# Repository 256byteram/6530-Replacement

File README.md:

# 6530 Replacement

Replaces the 6530 ICs found on early revision Allied Leisure pinball machines.

## Components

Please note these designs and instructions come with absolutely no warranty, implied or otherwise. I write these instructions assuming the builder has experience in assembling electronics.

You will need:

- x1 27C64 EPROM (or equivalent)

- x1 28 pin DIP IC socket

- x2 6532 IC's

- x5 40 pin IC socket - Dual wipe, **not machined**

- x1 74LS42 DIP IC

- x1 16 pin DIP IC socket

- x1 74LS11 DIP IC

- x2 74LS00 DIP IC

- x3 14 pin DIP IC socket

- x6 1N4148 silicon diodes

- x1 2N7000 transistor

- x3 1k ohm 1/4W resistors

- x1 1k x6 resistor network (or alternatively an additional 6 1k ohm 1/4W resistors)

- x6 100nF 50V monolithic capacitors

- x100 pin headers to fit the original sockets on the CPU board (5 rows of 20 pins)

- Alternatively: x5 stackable headers for the ESP32 [Sparkfun part number PRT-14311](https://www.sparkfun.com/esp32-thing-stackable-header-set.html). These won't damage IC sockets. See *Construction Notes* below.

To have these boards manufactured, it should be as simple as zipping the 6530-Replacement-Gerber folder and submitting them to a PCB manufacturer. The board dimensions are 100.3 x 100.3mm

## ROMs

I can not host the ROM image here as they are copyrighted. I have supplied a 1k blank image to assist with generating the required ROM image.

There are three ROM binaries I was supplied with, one each from the three original 6530's:

- EE1712_82219_DG_MOS6530_009.bin

- EE1712_82219_DG_MOS6530_010.bin

- EE1712_82219_DG_MOS6530_011.bin

To generate a ROM binary for the board on Linux or Mac in the terminal:

`cat Blank1k.bin Blank1k.bin Blank1k.bin EE1712_82219_DG_MOS6530_009.bin Blank1k.bin EE1712_82219_DG_MOS6530_010.bin EE1712_82219_DG_MOS6530_011.bin Blank1k.bin > AdaptorROM.bin`

And on the Windows command prompt:

`copy /b Blank1k.bin+Blank1k.bin+Blank1k.bin+EE1712_82219_DG_MOS6530_009.bin+Blank1k.bin+EE1712_82219_DG_MOS6530_010.bin+EE1712_82219_DG_MOS6530_011.bin+Blank1k.bin AdaptorROM.bin`

You will first need to `cd` to the directory the ROMs are in. This will give you an 8kB ROM image ready to burn to a 27C64 or equivalent EPROM.

**To use a 27C256 or similar EPROM** join pins 26 and 27 together on U8 of the Replacement board (the EPROM) with some solder.

To generate the required binary, create the `AdaptorROM.bin` file as previously instructed, then:

`cat AdaptorROM.bin AdaptorROM.bin AdaptorROM.bin AdaptorROM.bin > AdaptorROM32k.bin`

or on Windows:

`copy /b AdaptorROM.bin+AdaptorROM.bin+AdaptorROM.bin+AdaptorROM.bin AdaptorROM32k.bin`

## Construction notes

I recommend first replacing, at minimum, the three original 6530 IC sockets on the main board with dual wipe sockets. **Do not use machined sockets.** Ideally, all sockets should be replaced.

The headers need to be installed **before the IC sockets on the Replacement board are installed**.

If you are using ESP32 stackable headers, they won't damage the IC sockets on the main board, however they are more complicated to solder. Install all headers in the board from the component side, then flip the board so the black housings of the headers are on a flat surface. They will align themselves vertically. They can now be soldered. It will be easier if each header has one pin soldered first to keep it from moving.

When the pins are soldered, the black housing of the headers can be removed with a small pair of pliers. Once the housing starts to move it will release easily. The pins remaining **where the housing was removed** can be cut off. You should be left with the pins **on the solder side of the board**.

If you are using regular pin headers, they will tend to damage the IC sockets on the main board. I recommend replacing the original sockets with new **dual wipe** sockets. **Do not use machined IC sockets**. They need to be installed from the solder side of the board and soldered on the component side. **Make sure the pins are aligned vertically**. Solder one pin in place, then melt the solder again while aligning the header. The header won't move after the solder has cooled.

Construction from then on should be straight forward, following the usual rules.

If you are using a resistor network for RN1, the dot needs to align with the square pad.

## Installation

Installing the board has several issues which need to be considered. The main one is confusion over how it plugs into the sockets on the main board. **The top row of the IC3 socket - pins 21 through 40 - should not connect to anything.** All other pins should line up with the sockets. Check and re-check alignment before inserting the board.

## Pull-up Resistors

If you are using CMOS variant MC6821 GPIO chips, you will **need** to install pull-up resistors to the following pins and +5V:

- IC1 - Pins 2-9

- IC4 - Pins 2-5, 19

- IC7 - Pins 2-9, 39, 40

- IC8 - Pins 18, 19, 39, 40

This is because the original MOS 6520's would naturally float to a logic high. The MC6821's do not, instead they pick up any noise. **The machine will not run without these resistors**.

## Bodge Wires and Cuts

Please **do not** modify your board if there are no bodge wires, as it is the newer revision. This information is provided as a reference for early revision boards that needed the modifications. They are as follows:

**IC4:**

- Pin 9 -> Pin 18

**IC8:**

- Pin 10 -> IC29 pins 10, 9

- Pin 11 -> IC40 pin 1

- Pin 12 -> IC40 pin 2

- Pin 13 -> IC40 pin 4

- Pin 14 -> IC40 pin 5

**IC29:**

- Pins 1, 2 -> J2-W (originally wired to IC4 pin 28)

- Pin 3 -> Pin 5

- Pin 4 -> IC40 pin 6

- Pin 8 -> IC40 pin 3

The following traces are **cut**:

**IC4:**

- Pin 9 -> J1 (cut near J1)

- Pin 18 (cut near pin and on trace near J2)

- Pin 19 (cut near pin)

**IC29:**

- Pins 1, 2 -> IC40 pin 2

- Pin 5 -> IC40 pin 1

- Pin 13 -> IC40 pin 3 (cut near via)

## Protection Diodes

1N4007 diodes should be installed in **all** resistor locations near J2 and J3. The anode (not striped) should connect to 6V/24V GND in the middle of the array, i.e. the diodes should be pointing away from ground and to the signals.

Good luck!

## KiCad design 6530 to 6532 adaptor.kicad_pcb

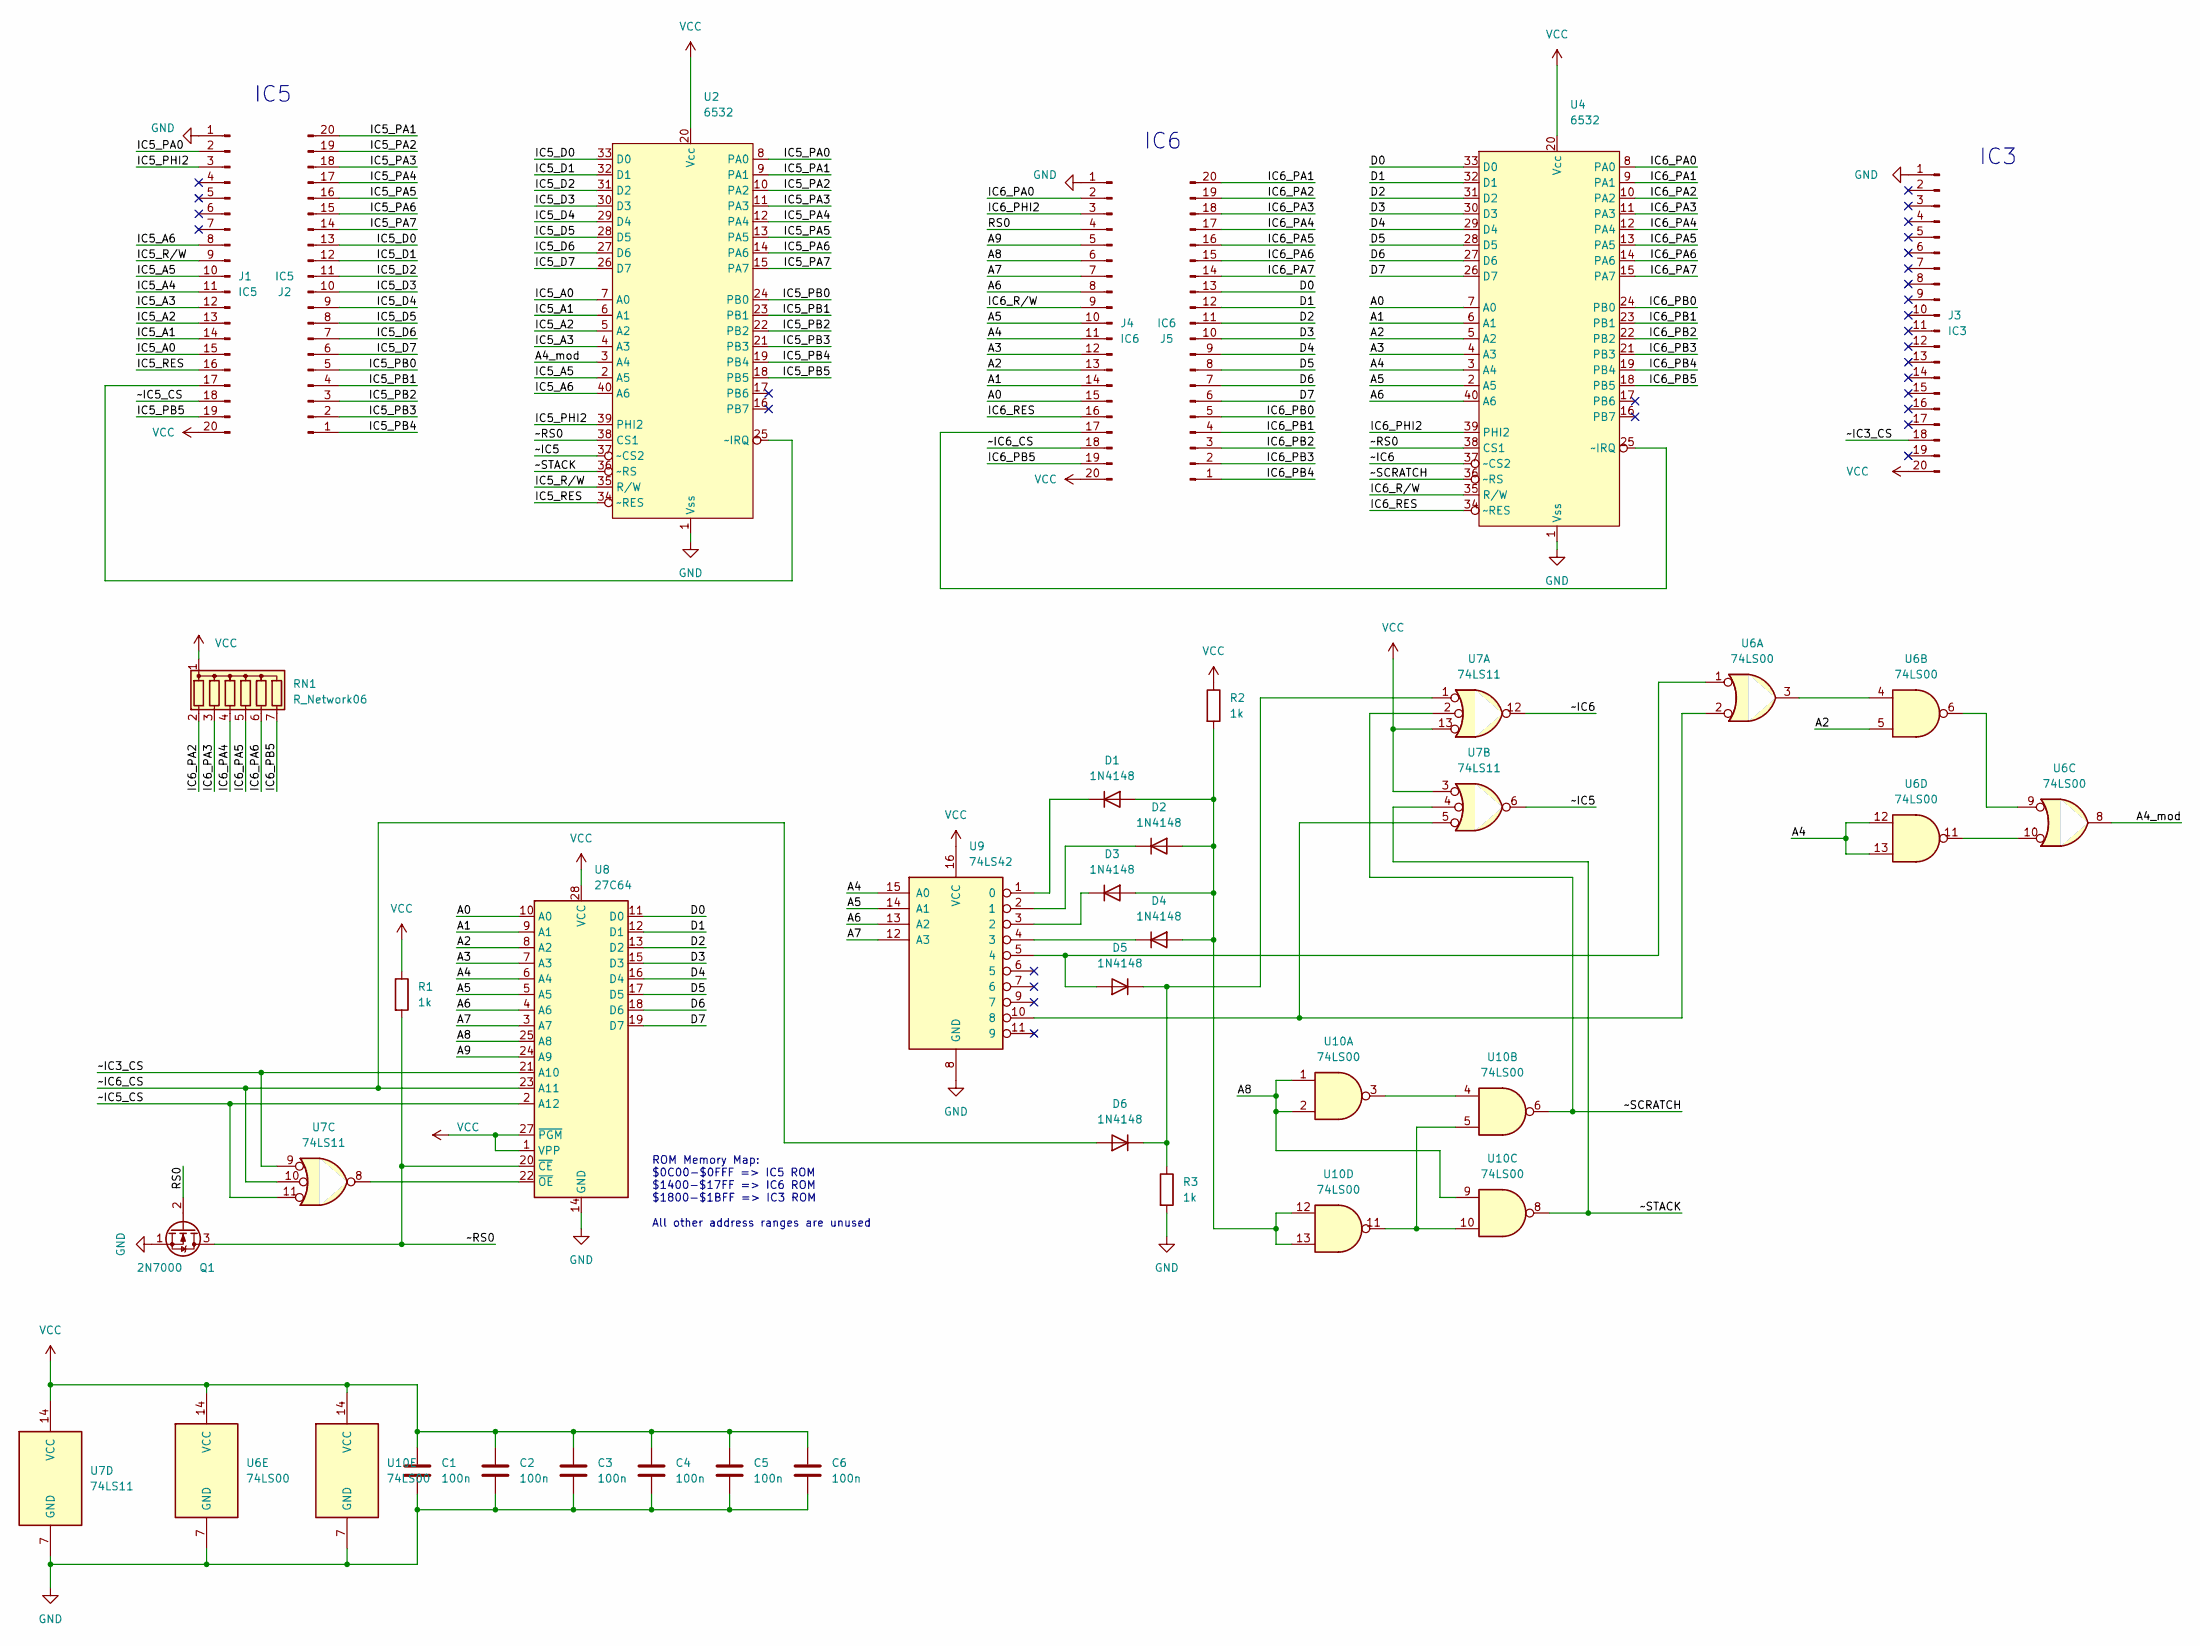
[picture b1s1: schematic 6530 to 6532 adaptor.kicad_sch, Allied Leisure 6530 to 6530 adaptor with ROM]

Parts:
C1, C2, C3, C4, C5, C6: 100n; C_Disc_D5.0mm_W2.5mm_P5.00mm
D1, D2, D3, D4, D5, D6: 1N4148; D_DO-34_SOD68_P7.62mm_Horizontal
J1, J2: IC5; PinHeader_1x20_P2.54mm_Vertical
J3: IC3; PinHeader_1x20_P2.54mm_Vertical
J4, J5: IC6; PinHeader_1x20_P2.54mm_Vertical
Q1: 2N7000; TO-92L_Inline_Wide
R1, R2, R3: 1k; R_Axial_DIN0207_L6.3mm_D2.5mm_P10.16mm_Horizontal
RN1: R_Network06; R_Array_SIP7
U2, U4: 6532; DIP-40_W15.24mm_Socket_LongPads
U6, U10: 74LS00; DIP-14_W7.62mm_Socket_LongPads
U7: 74LS11; DIP-14_W7.62mm_Socket_LongPads
U8: 27C64; DIP-28_W15.24mm_Socket_LongPads
U9: 74LS42; DIP-16_W7.62mm_Socket_LongPads

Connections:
/A0: J4.15, U4.7 (A0), U8.10 (A0)
/A1: J4.14, U4.6 (A1), U8.9 (A1)
/A2: J4.13, U4.5 (A2), U6.5, U8.8 (A2)
/A3: J4.12, U4.4 (A3), U8.7 (A3)
/A4: J4.11, U4.3 (A4), U6.12, U6.13, U8.6 (A4), U9.15 (A0)
/A4_mod: U2.3 (A4), U6.8
/A5: J4.10, U4.2 (A5), U8.5 (A5), U9.14 (A1)
/A6: J4.8, U4.40 (A6), U8.4 (A6), U9.13 (A2)
/A7: J4.7, U8.3 (A7), U9.12 (A3)
/A8: J4.6, U8.25 (A8), U10.1, U10.2, U10.9
/A9: J4.5, U8.24 (A9)
/D0: J5.13, U4.33 (D0), U8.11 (D0)
/D1: J5.12, U4.32 (D1), U8.12 (D1)
/D2: J5.11, U4.31 (D2), U8.13 (D2)
/D3: J5.10, U4.30 (D3), U8.15 (D3)
/D4: J5.9, U4.29 (D4), U8.16 (D4)
/D5: J5.8, U4.28 (D5), U8.17 (D5)
/D6: J5.7, U4.27 (D6), U8.18 (D6)
/D7: J5.6, U4.26 (D7), U8.19 (D7)
/IC5_A0: J1.15, U2.7 (A0)
/IC5_A1: J1.14, U2.6 (A1)
/IC5_A2: J1.13, U2.5 (A2)
/IC5_A3: J1.12, U2.4 (A3)
/IC5_A4: J1.11
/IC5_A5: J1.10, U2.2 (A5)
/IC5_A6: J1.8, U2.40 (A6)
/IC5_D0: J2.13, U2.33 (D0)
/IC5_D1: J2.12, U2.32 (D1)
/IC5_D2: J2.11, U2.31 (D2)
/IC5_D3: J2.10, U2.30 (D3)
/IC5_D4: J2.9, U2.29 (D4)
/IC5_D5: J2.8, U2.28 (D5)
/IC5_D6: J2.7, U2.27 (D6)
/IC5_D7: J2.6, U2.26 (D7)
/IC5_PA0: J1.2, U2.8 (PA0)
/IC5_PA1: J2.20, U2.9 (PA1)
/IC5_PA2: J2.19, U2.10 (PA2)
/IC5_PA3: J2.18, U2.11 (PA3)
/IC5_PA4: J2.17, U2.12 (PA4)
/IC5_PA5: J2.16, U2.13 (PA5)
/IC5_PA6: J2.15, U2.14 (PA6)
/IC5_PA7: J2.14, U2.15 (PA7)
/IC5_PB0: J2.5, U2.24 (PB0)
/IC5_PB1: J2.4, U2.23 (PB1)
/IC5_PB2: J2.3, U2.22 (PB2)
/IC5_PB3: J2.2, U2.21 (PB3)
/IC5_PB4: J2.1, U2.19 (PB4)
/IC5_PB5: J1.19, U2.18 (PB5)
/IC5_PHI2: J1.3, U2.39 (PHI2)
/IC5_RES: J1.16, U2.34 (~RES)
/IC5_R/W: J1.9, U2.35 (R/W)
/IC6_PA0: J4.2, U4.8 (PA0)
/IC6_PA1: J5.20, U4.9 (PA1)
/IC6_PA2: J5.19, RN1.2 (R1), U4.10 (PA2)
/IC6_PA3: J5.18, RN1.3 (R2), U4.11 (PA3)
/IC6_PA4: J5.17, RN1.4 (R3), U4.12 (PA4)
/IC6_PA5: J5.16, RN1.5 (R4), U4.13 (PA5)
/IC6_PA6: J5.15, RN1.6 (R5), U4.14 (PA6)
/IC6_PA7: J5.14, U4.15 (PA7)
/IC6_PB0: J5.5, U4.24 (PB0)
/IC6_PB1: J5.4, U4.23 (PB1)
/IC6_PB2: J5.3, U4.22 (PB2)
/IC6_PB3: J5.2, U4.21 (PB3)
/IC6_PB4: J5.1, U4.19 (PB4)
/IC6_PB5: J4.19, RN1.7 (R6), U4.18 (PB5)
/IC6_PHI2: J4.3, U4.39 (PHI2)
/IC6_RES: J4.16, U4.34 (~RES)
/IC6_R/W: J4.9, U4.35 (R/W)
/RS0: J4.4, Q1.2 (G)
/~IC3_CS: J3.18, U7.9, U8.21 (A10)
/~IC5: U2.37 (~CS2), U7.6
/~IC5_CS: J1.18, U7.11, U8.2 (A12)
/~IC6: U4.37 (~CS2), U7.12
/~IC6_CS: D6.2 (A), J4.18, U7.10, U8.23 (A11)
/~RS0: Q1.3 (D), R1.2, U2.38 (CS1), U4.38 (CS1), U8.20 (~CE)
/~SCRATCH: U4.36 (~RS), U7.2, U10.6
/~STACK: U2.36 (~RS), U7.4, U10.8
GND: C1.2, C2.2, C3.2, C4.2, C5.2, C6.2, J1.1, J3.1, J4.1, Q1.1 (S), R3.2, U2.1 (Vss), U4.1 (Vss), U6.7 (GND), U7.7 (GND), U8.14 (GND), U9.8 (GND), U10.7 (GND)
unnamed: D1.1 (K), U9.1 (0)
unnamed: D1.2 (A), D2.2 (A), D3.2 (A), D4.2 (A), R2.2, U10.12, U10.13
unnamed: D2.1 (K), U9.2 (1)
unnamed: D3.1 (K), U9.3 (2)
unnamed: D4.1 (K), U9.4 (3)
unnamed: D5.1 (K), D6.1 (K), R3.1, U7.1
unnamed: D5.2 (A), U6.1, U9.5 (4)
unnamed: J1.17, U2.25 (~IRQ)
unnamed: J4.17, U4.25 (~IRQ)
unnamed: U6.2, U7.5, U9.10 (8)
unnamed: U6.3, U6.4
unnamed: U6.6, U6.9
unnamed: U6.10, U6.11
unnamed: U7.8, U8.22 (~OE)
unnamed: U10.3, U10.4
unnamed: U10.5, U10.10, U10.11
VCC: C1.1, C2.1, C3.1, C4.1, C5.1, C6.1, J1.20, J3.20, J4.20, R1.1, R2.1, RN1.1 (common), U2.20 (Vcc), U4.20 (Vcc), U6.14 (VCC), U7.3, U7.13, U7.14 (VCC), U8.1 (VPP), U8.27 (~PGM), U8.28 (VCC), U9.16 (VCC), U10.14 (VCC)

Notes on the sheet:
ROM Memory Map: $0C00-$0FFF => IC5 ROM $1400-$17FF => IC6 ROM $1800-$1BFF => IC3 ROM All other address ranges are unused
IC6
IC5
IC3

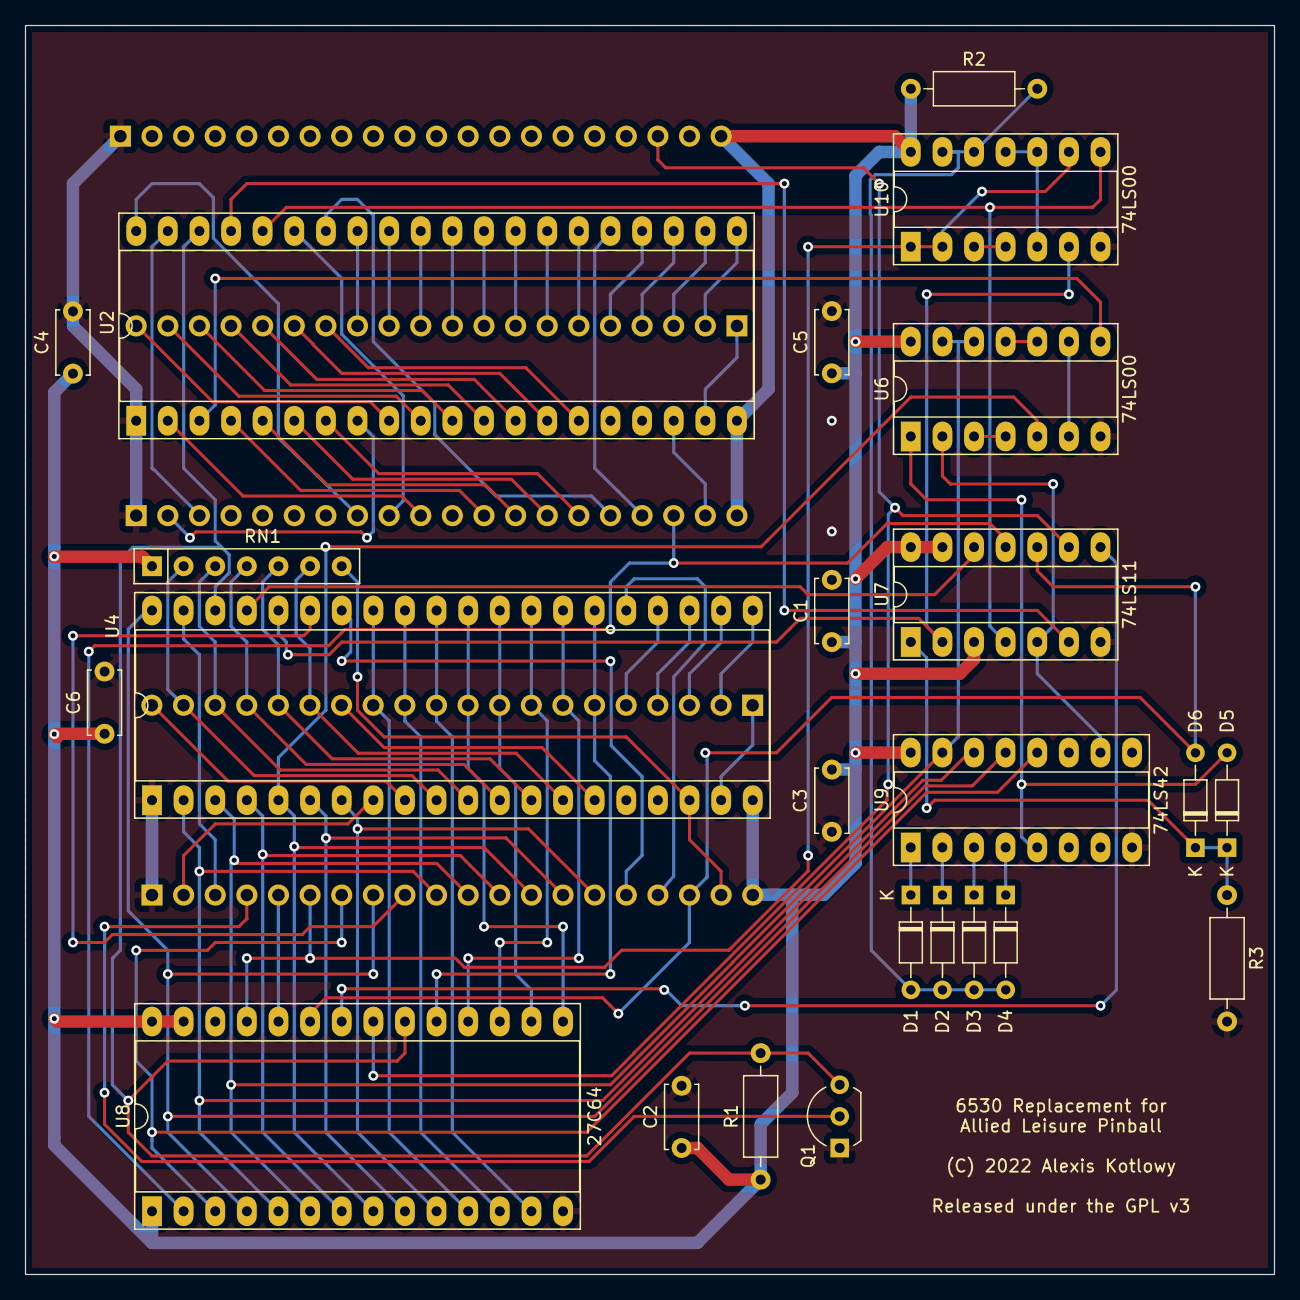
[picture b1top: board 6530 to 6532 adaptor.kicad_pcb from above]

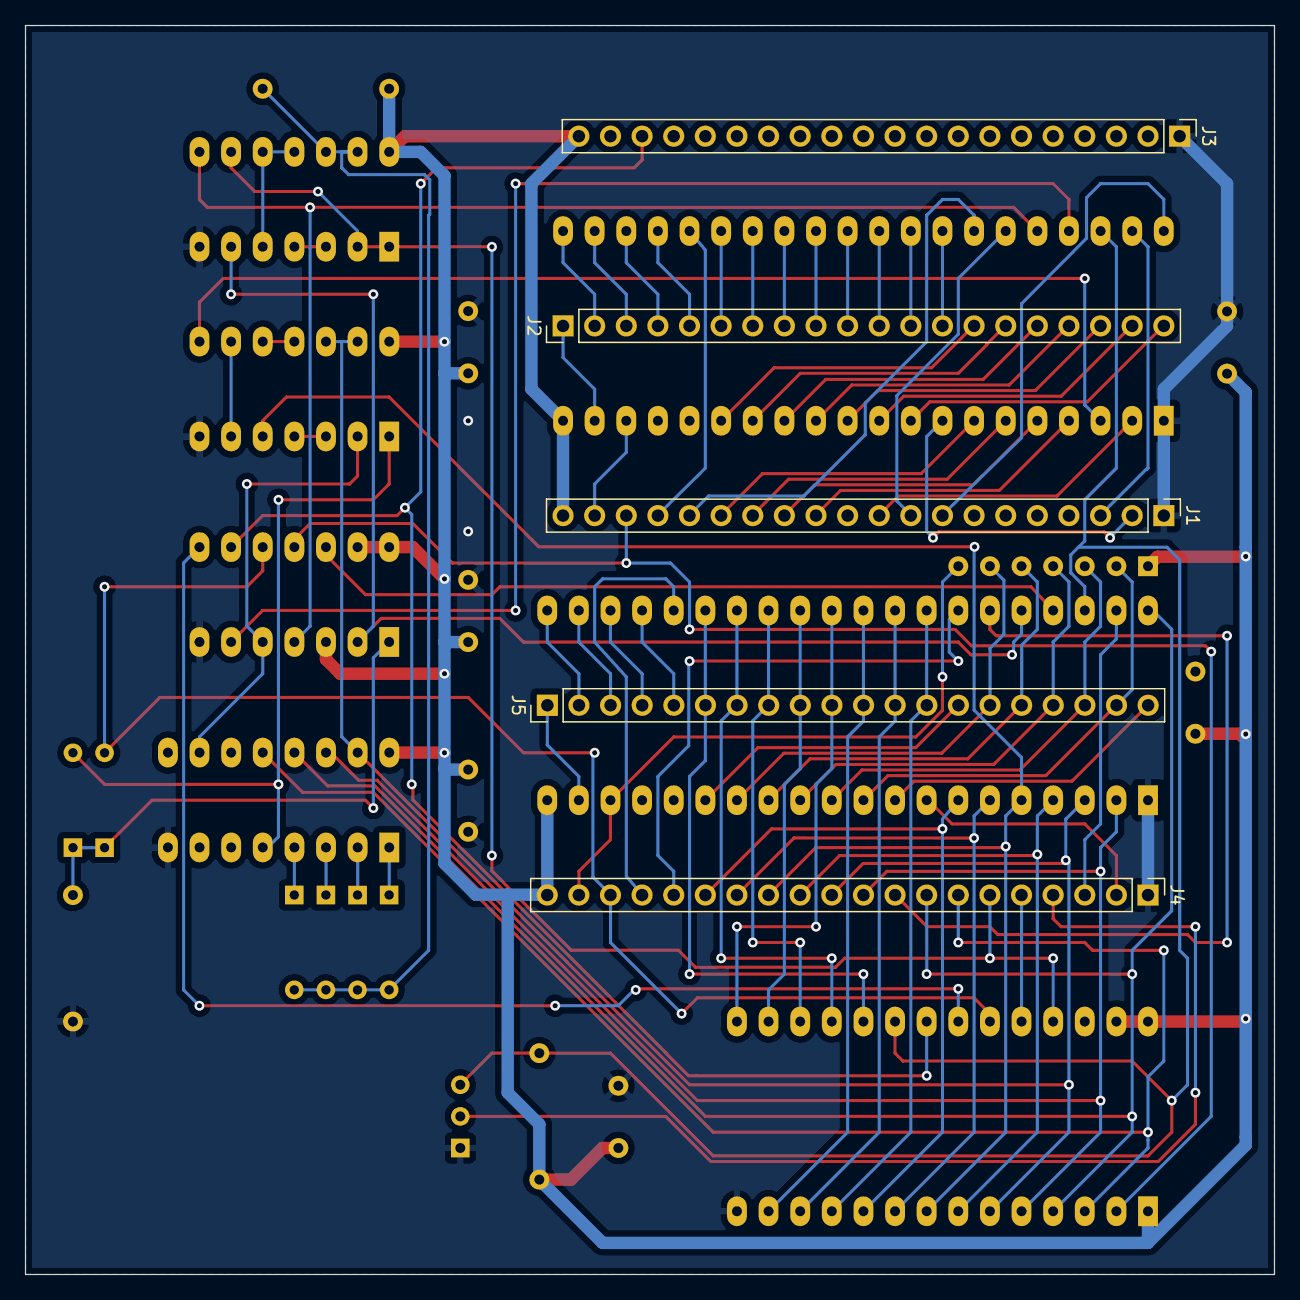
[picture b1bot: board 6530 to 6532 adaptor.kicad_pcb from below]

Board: 2 copper layers, 100.3 x 100.3 mm, 29 parts (5 on the bottom side), 94 nets.

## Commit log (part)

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2022-04-12 Initial push
2022-04-12 Update schematic PDF
2022-04-12 Update name on schematic
2022-05-03 Updated readme and ROM files
2025-06-30 Update to documentation

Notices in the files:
6530 to 6532 adaptor.kicad_pcb:
(C) 2022 Alexis Kotlowy
Released under the GPL v3
6530 to 6532 adaptor.kicad_sch:
Copyright (C) 2022 Alexis Kotlowy
https://www.gnu.org/licenses/gpl-3.0.en.html
Released under the GPL v3 license
